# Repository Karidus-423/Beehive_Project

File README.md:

# Beehive Project for Kentucky State University
___
The folders build up the project and each of them is responsible for a single 
aspect of it.

- [Datalogger_Beehive](https://github.com/Karidus-423/Beehive_Project/tree/main/Datalogger_Beehive) contains the arduino scripts and the schematics for Pcbs so that the can be printed and the data to get collected.
- [Research_Beehive](https://github.com/Karidus-423/Beehive_Project/tree/main/Research_Beehive) used to analyze the data and make graphs that can be used for science presentations and conferences.
- [Webapp_Beehive](https://github.com/Karidus-423/Beehive_Project/tree/main/Webapp_Beehive) where the webapp in which the output of the Datalogger will be used so that we areble to visualize the recordings of the data.

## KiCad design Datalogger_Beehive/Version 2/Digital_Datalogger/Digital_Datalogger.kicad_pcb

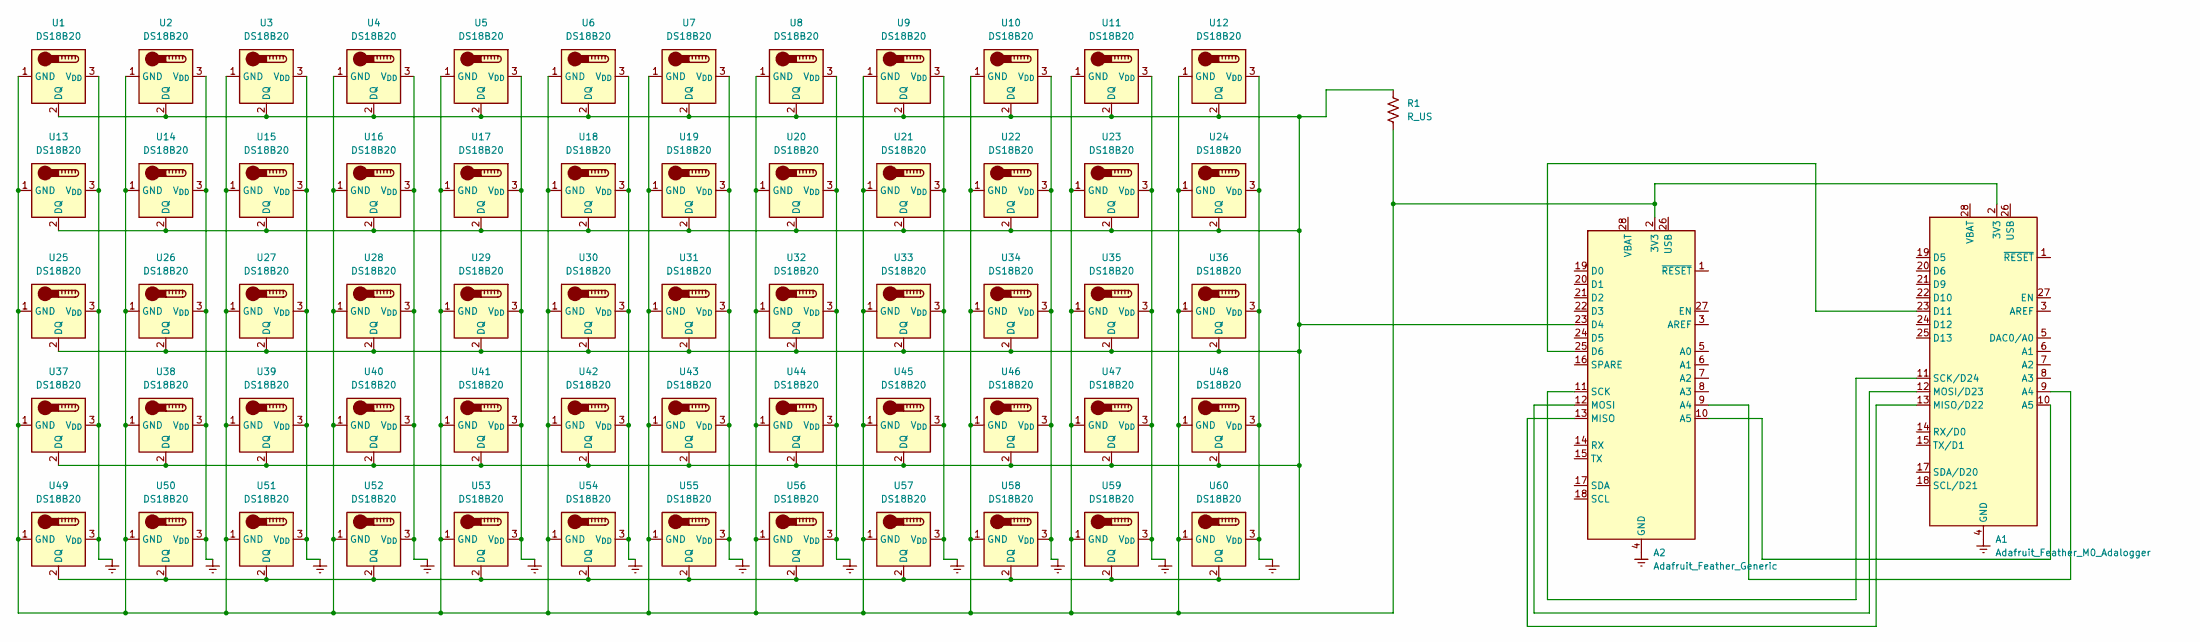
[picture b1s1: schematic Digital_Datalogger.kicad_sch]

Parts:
A1: Adafruit_Feather_M0_Adalogger; Adafruit_Feather
A2: Adafruit_Feather_Generic; Adafruit_Feather
R1: R_US; R_Axial_DIN0614_L14.3mm_D5.7mm_P25.40mm_Horizontal
U1, U2, U3, U4, U5, U6, U7, U8, U9, U10, U11, U12, U13, U14, U15, U16, U17, U18, U19, U20, U21, U22, U23, U24, U25, U26, U27, U28, U29, U30, U31, U32, U33, U34, U35, U36, U37, U38, U39, U40, U41, U43, U44, U45, U46, U47, U48, U49, U51, U52, U53, U54, U55, U56, U57, U58, U59, U60: DS18B20; TO-92_Inline
U42, U50: DS18B20; DS18B20 Connector

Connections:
Earth: A1.4 (GND), A1.16 (GND), A2.4 (GND), U1.3 (V_{DD}), U2.3 (V_{DD}), U3.3 (V_{DD}), U4.3 (V_{DD}), U5.3 (V_{DD}), U6.3 (V_{DD}), U7.3 (V_{DD}), U8.3 (V_{DD}), U9.3 (V_{DD}), U10.3 (V_{DD}), U11.3 (V_{DD}), U12.3 (V_{DD}), U13.3 (V_{DD}), U14.3 (V_{DD}), U15.3 (V_{DD}), U16.3 (V_{DD}), U17.3 (V_{DD}), U18.3 (V_{DD}), U19.3 (V_{DD}), U20.3 (V_{DD}), U21.3 (V_{DD}), U22.3 (V_{DD}), U23.3 (V_{DD}), U24.3 (V_{DD}), U25.3 (V_{DD}), U26.3 (V_{DD}), U27.3 (V_{DD}), U28.3 (V_{DD}), U29.3 (V_{DD}), U30.3 (V_{DD}), U31.3 (V_{DD}), U32.3 (V_{DD}), U33.3 (V_{DD}), U34.3 (V_{DD}), U35.3 (V_{DD}), U36.3 (V_{DD}), U37.3 (V_{DD}), U38.3 (V_{DD}), U39.3 (V_{DD}), U40.3 (V_{DD}), U41.3 (V_{DD}), U42.3 (V_{DD}), U43.3 (V_{DD}), U44.3 (V_{DD}), U45.3 (V_{DD}), U46.3 (V_{DD}), U47.3 (V_{DD}), U48.3 (V_{DD}), U49.3 (V_{DD}), U50.3 (V_{DD}), U51.3 (V_{DD}), U52.3 (V_{DD}), U53.3 (V_{DD}), U54.3 (V_{DD}), U55.3 (V_{DD}), U56.3 (V_{DD}), U57.3 (V_{DD}), U58.3 (V_{DD}), U59.3 (V_{DD}), U60.3 (V_{DD})
unnamed: A1.2 (3V3), A2.2 (3V3), R1.2, U1.1 (GND), U2.1 (GND), U3.1 (GND), U4.1 (GND), U5.1 (GND), U6.1 (GND), U7.1 (GND), U8.1 (GND), U9.1 (GND), U10.1 (GND), U11.1 (GND), U12.1 (GND), U13.1 (GND), U14.1 (GND), U15.1 (GND), U16.1 (GND), U17.1 (GND), U18.1 (GND), U19.1 (GND), U20.1 (GND), U21.1 (GND), U22.1 (GND), U23.1 (GND), U24.1 (GND), U25.1 (GND), U26.1 (GND), U27.1 (GND), U28.1 (GND), U29.1 (GND), U30.1 (GND), U31.1 (GND), U32.1 (GND), U33.1 (GND), U34.1 (GND), U35.1 (GND), U36.1 (GND), U37.1 (GND), U38.1 (GND), U39.1 (GND), U40.1 (GND), U41.1 (GND), U42.1 (GND), U43.1 (GND), U44.1 (GND), U45.1 (GND), U46.1 (GND), U47.1 (GND), U48.1 (GND), U49.1 (GND), U50.1 (GND), U51.1 (GND), U52.1 (GND), U53.1 (GND), U54.1 (GND), U55.1 (GND), U56.1 (GND), U57.1 (GND), U58.1 (GND), U59.1 (GND), U60.1 (GND)
unnamed: A1.9 (A4), A2.9 (A4)
unnamed: A1.10 (A5), A2.10 (A5)
unnamed: A1.23 (D11), A2.25 (D6)
unnamed: A1.13 (MISO/D22), A2.13 (MISO)
unnamed: A1.12 (MOSI/D23), A2.12 (MOSI)
unnamed: A1.11 (SCK/D24), A2.11 (SCK)
unnamed: A2.23 (D4), R1.1, U1.2 (DQ), U2.2 (DQ), U3.2 (DQ), U4.2 (DQ), U5.2 (DQ), U6.2 (DQ), U7.2 (DQ), U8.2 (DQ), U9.2 (DQ), U10.2 (DQ), U11.2 (DQ), U12.2 (DQ), U13.2 (DQ), U14.2 (DQ), U15.2 (DQ), U16.2 (DQ), U17.2 (DQ), U18.2 (DQ), U19.2 (DQ), U20.2 (DQ), U21.2 (DQ), U22.2 (DQ), U23.2 (DQ), U24.2 (DQ), U25.2 (DQ), U26.2 (DQ), U27.2 (DQ), U28.2 (DQ), U29.2 (DQ), U30.2 (DQ), U31.2 (DQ), U32.2 (DQ), U33.2 (DQ), U34.2 (DQ), U35.2 (DQ), U36.2 (DQ), U37.2 (DQ), U38.2 (DQ), U39.2 (DQ), U40.2 (DQ), U41.2 (DQ), U42.2 (DQ), U43.2 (DQ), U44.2 (DQ), U45.2 (DQ), U46.2 (DQ), U47.2 (DQ), U48.2 (DQ), U49.2 (DQ), U50.2 (DQ), U51.2 (DQ), U52.2 (DQ), U53.2 (DQ), U54.2 (DQ), U55.2 (DQ), U56.2 (DQ), U57.2 (DQ), U58.2 (DQ), U59.2 (DQ), U60.2 (DQ)

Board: 2 copper layers, 63 parts (0 on the bottom side), 9 nets, no tracks yet.

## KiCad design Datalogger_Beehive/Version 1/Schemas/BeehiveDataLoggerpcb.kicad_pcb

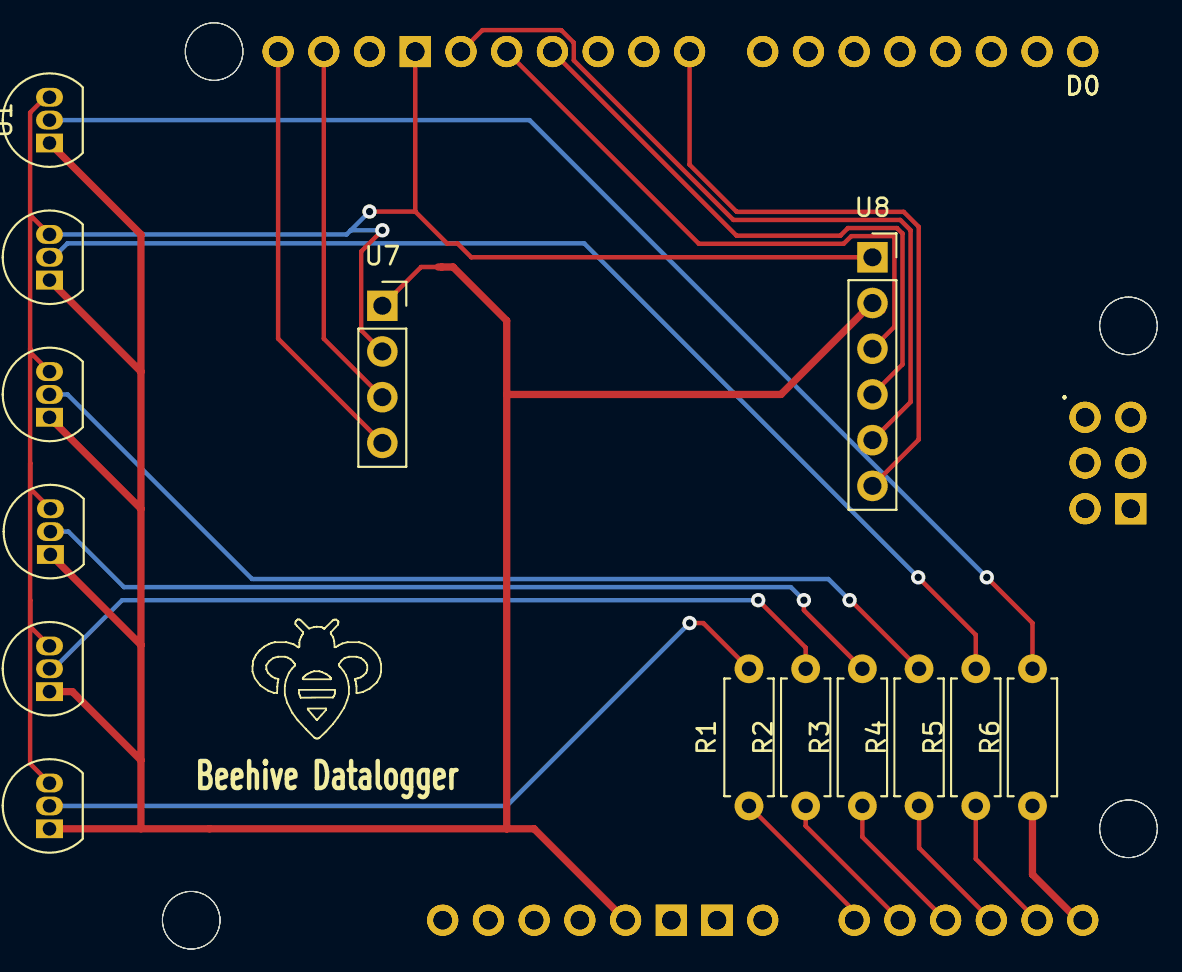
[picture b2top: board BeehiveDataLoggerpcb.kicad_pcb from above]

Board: 2 copper layers, 16 parts (0 on the bottom side), 20 nets.

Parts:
A1, A1#2: Arduino_Uno_R3_Shield
R1, R2, R3, R4, R5, R6: R; R_Axial_DIN0207_L6.3mm_D2.5mm_P7.62mm_Horizontal
U1, U2, U3, U4, U5, U6: LM35-LP; TO-92_Inline
U7: PinSocket_1x04_P2.54mm_Vertical
U8: PinSocket_1x06_P2.54mm_Vertical

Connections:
unnamed: A1.5V1 (5V), A1#2.5V1 (5V), U1.1 (+V_{S}), U2.1 (+V_{S}), U3.1 (+V_{S}), U4.1 (+V_{S}), U5.1 (+V_{S}), U6.1 (+V_{S}), U7.1 (Vcc), U8.2 (Vcc)
unnamed: A1.A0, A1#2.A0, R1.1
unnamed: A1.A1, A1#2.A1, R2.1
unnamed: A1.A2, A1#2.A2, R3.1
unnamed: A1.A3, A1#2.A3, R4.1
unnamed: A1.A4, A1#2.A4, R5.1
unnamed: A1.A5, A1#2.A5, R6.1
unnamed: A1.GND1 (GND), A1#2.GND1 (GND), U1.3 (GND), U2.3 (GND), U3.3 (GND), U4.3 (GND), U5.3 (GND), U6.3 (GND), U7.2 (GND), U8.1 (GND)
unnamed: R6.2, U1.2 (V_{OUT})
unnamed: R5.2, U2.2 (V_{OUT})
unnamed: R4.2, U3.2 (V_{OUT})
unnamed: R3.2, U4.2 (V_{OUT})
unnamed: R2.2, U5.2 (V_{OUT})
unnamed: R1.2, U6.2 (V_{OUT})
unnamed: A1.SCL, A1#2.SCL, U7.4 (SCL)
unnamed: A1.SDA, A1#2.SDA, U7.3 (SDA)
unnamed: A1.D8, A1#2.D8, U8.6 (CS)
unnamed: A1.D12, A1#2.D12, U8.3 (MISO)
unnamed: A1.D11, A1#2.D11, U8.4 (MOSI)
unnamed: A1.D13, A1#2.D13, U8.5 (SCK)

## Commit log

2024-01-04 New File Structure for Beehive Project
2024-01-04 Renamed Folder
    Made new directory for digital sensors datalogger
2024-01-04 Merge
2024-01-11 Added 3D models and Schemas
2024-01-24 WIP
    First appendation towards adding custom temperature filtering via a user friendly text box
2024-02-06 Added code for digital sensors
2024-02-23 Tweaking
2024-03-03 migrate
2024-04-12 nix working
2024-04-22 board
2024-05-14 pcb update
2024-05-16 enclosure adding
2024-05-24 docs
2024-05-24 readme
2024-05-29 datalogger readme
2024-06-13 sensor_data from datalogger
